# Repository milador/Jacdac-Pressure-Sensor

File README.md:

# Jacdac-Pressure-Sensor
A <a href="https://microsoft.github.io/jacdac-docs/">Jacdac</a> Pressure Sensor Module based on <a href="https://www.st.com/en/mems-and-sensors/lps33hw.html">LPS33HW</a> Absolute digital Pressure Sensor.

## Jacdac Dashboard: 

## Top View: 

## Bottom View:

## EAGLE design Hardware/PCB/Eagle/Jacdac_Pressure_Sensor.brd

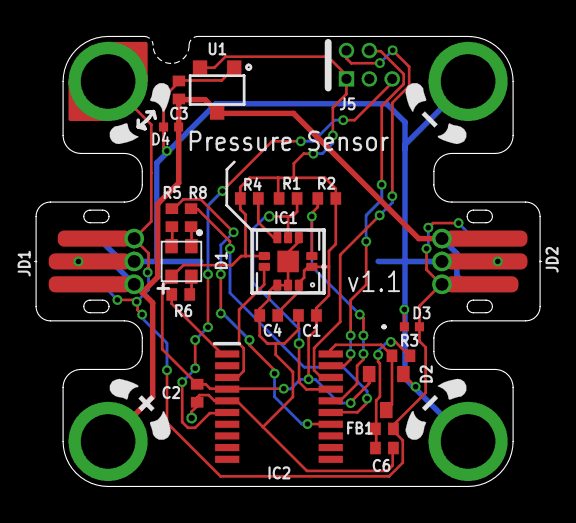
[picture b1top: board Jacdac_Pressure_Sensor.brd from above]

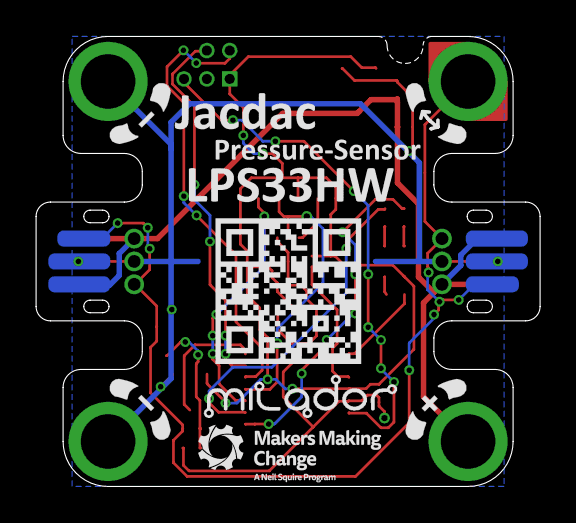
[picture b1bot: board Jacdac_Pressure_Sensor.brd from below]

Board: 2 copper layers, 28.0 x 25.0 mm, 32 parts (5 on the bottom side), 19 nets.

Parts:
C1, C4: 100nF; 0402
C2, C3: 4.7uF; 0402
C6: 33pF; 0402
D1: C108793; LED-RGB-2121
D2: BAT54S-23-3; SOT23-3
D3, D4: RCLAMP0521PATCT; DIODE-ZENER-0402
FB1: 1k@100MHz; 0402
IC1: LPS33HWTR; PQFN60P330X330X290-11N
IC2: STM32G030F6P6; SOP65P640X120-20N
J1: JD; M3-HOLE-DATA
J2: PWR; M3-HOLE-PWR
J3, J4: GND; M3-HOLE-GND
J5: HACK-CONNECT-5; HC5-22-62
JD1, JD2: JACDAC-EDGE-OUTIE; JD-EDGE-OUTIE
LABEL_DEVICE: MILADOR-JACDAC-DEVICE-PS; JACDAC-PRESSURE-SENSOR
LABEL_LOGO1: MILADOR-LOGO-SM; MILADOR_LOGO2
LABEL_LOGO2: MMC_LOGO-XSM; MMC_X-SMALL_LOGO
LABEL_LPS33: MILADOR-JACDAC-DEVICE-LPS33HW; JACDAC-LPS33HW
LABEL_QRCODE: MILADOR-QR-CODE-JACDAC-GITHUB-PS; MILADOR_QR_JACDAC_PS
R1, R2, R4: 10k; 0402
R3, R5: 220R; 0402
R6: 470R; 0402
R8: 150R; 0402
U1: XC6206; SOT23-3-W

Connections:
GND: C1.2, C2.2, C3.2, C4.2, C6.2, D2.1, D3.1, D4.1, IC1.3, IC1.8, IC1.9, IC1.EP, IC2.5, J3.H, J4.H, J5.3, JD1.2, JD1.5, JD1.P$2, JD1.P$4, JD2.2, JD2.5, JD2.P$2, JD2.P$4, U1.1
INT: IC1.7, IC2.3
JD: D2.3, IC2.20, R3.1
JD5V: C3.1, D4.2, J2.H, JD1.3, JD1.4, JD1.P$1, JD2.3, JD2.4, JD2.P$1, U1.3
JDF: D3.2, FB1.2, J1.H, JD1.1, JD1.6, JD1.P$3, JD2.1, JD2.6, JD2.P$3
LED_B: IC2.1, R6.1
LED_G: IC2.14, R5.1
LED_R: IC2.15, R8.1
unnamed: C6.1, FB1.1, R3.2
unnamed: D1.B-, R6.2
unnamed: D1.R-, R8.2
unnamed: D1.G-, R5.2
RESET: IC2.6, J5.5
SA0: IC1.5, R4.1
SCL: IC1.2, IC2.16, R2.1
SDA: IC1.4, IC2.17, R1.1
SWCLK: IC2.19, J5.4
SWDIO: IC2.18, J5.2
VCC: C1.1, C2.1, C4.1, D1.PLUS, D2.2, IC1.1, IC1.6, IC1.10, IC2.4, J5.1, R1.2, R2.2, R4.2, U1.2

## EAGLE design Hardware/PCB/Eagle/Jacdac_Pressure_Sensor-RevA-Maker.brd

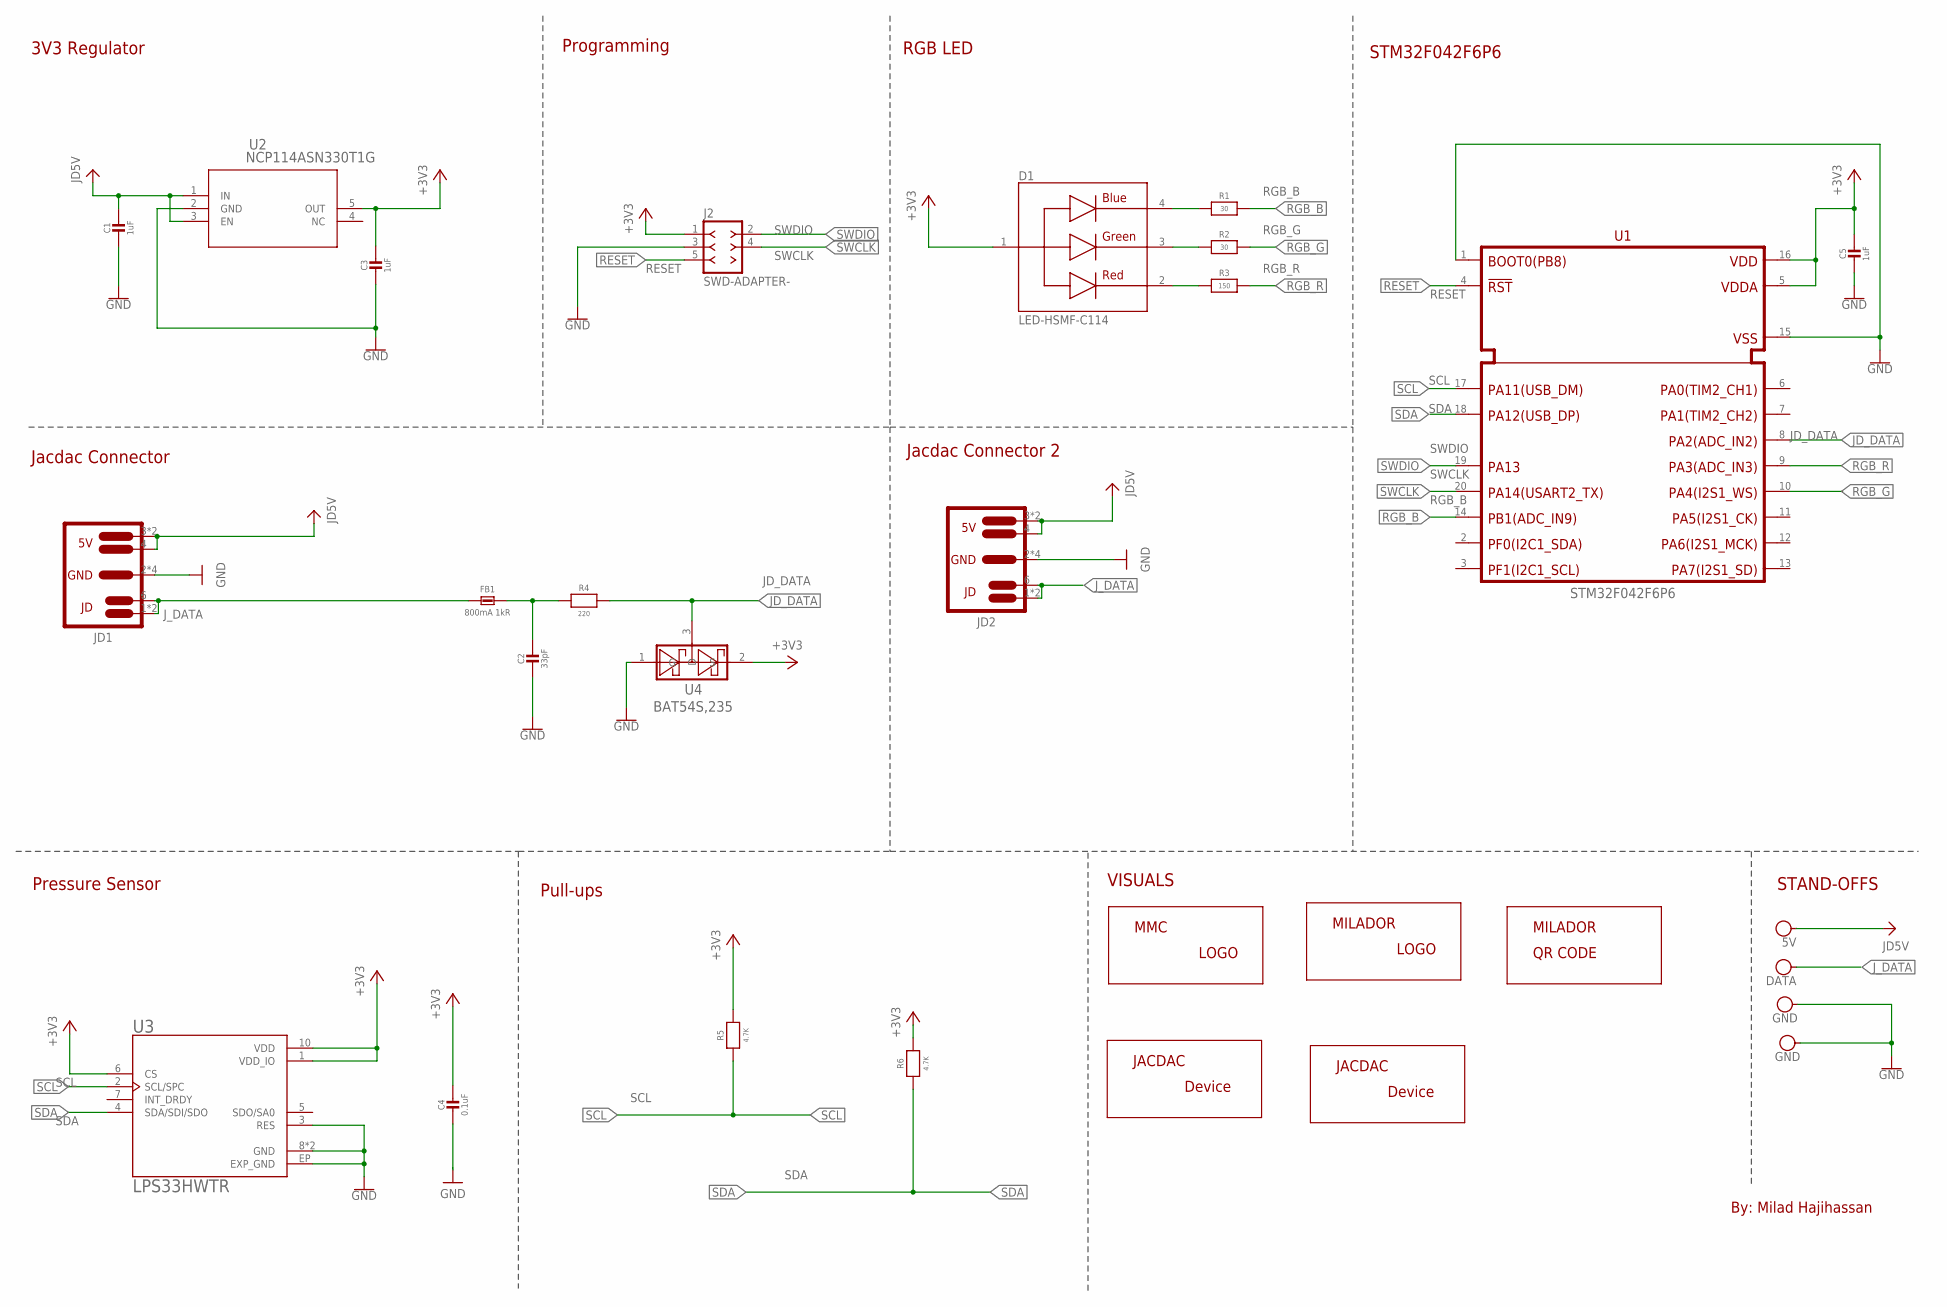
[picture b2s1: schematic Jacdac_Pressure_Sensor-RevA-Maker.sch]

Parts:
C1, C3: 1uF; 0603-NO
C2: 33pF; 0603
C4: 0.1uF; 0603-NO
C5: 1uF; 0603
D1: LED-HSMF-C114; DIOSC160X150X35-4N
FB1: 800mA 1kR; 0603-NO
J2: SWD-ADAPTER-; SWD-ADAPTER
J3: 5V; M3-HOLE-PWR-OUTL
J4: DATA; M3-HOLE-DATA-NOTCH
J5, J6: GND; M3-HOLE-GND
JD1, JD2: JACDAC-EDGE-OUTIE; JD-EDGE-OUTIE
LABEL_JACDAC_PS: MILADOR-JACDAC-DEVICE-PS; JACDAC-PRESSURE-SENSOR
LABEL_LPS33HW: MILADOR-JACDAC-DEVICE-LPS33HW; JACDAC-LPS33HW
LABEL_MILADOR: MILADOR-LOGO-; MILADOR_LOGO1
LABEL_QR_CODE: MILADOR-QR-CODE-JACDAC-GITHUB-PS; MILADOR_QR_JACDAC_PS
MMC_LOGO: MMC_LOGO-XSM; MMC_X-SMALL_LOGO
R1, R2: 30; 0603
R3: 150; 0603
R4: 220; 0603
R5, R6: 4.7K; 0603
U1: STM32F042F6P6; TSSOP20
U2: NCP114ASN330T1G; TSOP-5_ONS
U3: LPS33HWTR; PQFN60P330X330X290-11N
U4: BAT54S,235; SOT23-3

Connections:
+3V3: C3.1, C4.1, C5.1, D1.1, J2.1 (VCC_1), R5.2, R6.2, U1.5 (VDDA), U1.16 (VDD), U2.5 (OUT), U3.1 (VDD_IO), U3.6 (CS), U3.10 (VDD), U4.2 (S)
GND: C1.2, C2.2, C3.2, C4.2, C5.2, J2.3 (GND_3), J5.H, J6.H, JD1.2 (1), JD1.5 (1), JD1.P$2 (1), JD1.P$4 (1), JD2.2 (1), JD2.5 (1), JD2.P$2 (1), JD2.P$4 (1), U1.1 (BOOT0), U1.15 (VSS), U2.2 (GND), U3.3 (RES), U3.8 (GND), U3.9 (GND), U3.EP (EXP_GND), U4.1 (G)
JD5V: C1.1, J3.H, JD1.3, JD1.4, JD1.P$1 (3), JD2.3, JD2.4, JD2.P$1 (3), U2.1 (IN), U2.3 (EN)
JD_DATA: R4.2, U1.8 (PA2), U4.3 (D)
J_DATA: FB1.2, J4.H, JD1.1 (2), JD1.6, JD1.P$3 (2), JD2.1 (2), JD2.6, JD2.P$3 (2)
unnamed: D1.4, R1.1
unnamed: D1.3, R2.1
unnamed: D1.2, R3.1
unnamed: C2.1, FB1.1, R4.1
RESET: J2.5 (RESET_5), U1.4 (!RST)
RGB_B: R1.2, U1.14 (PB1)
RGB_G: R2.2, U1.10 (PA4)
RGB_R: R3.2, U1.9 (PA3)
SCL: R5.1, U1.17 (PA11), U3.2 (SCL/SPC)
SDA: R6.1, U1.18 (PA12), U3.4 (SDA/SDI/SDO)
SWCLK: J2.4 (SWCLK_4), U1.20 (PA14)
SWDIO: J2.2 (SWDIO_2), U1.19 (PA13)

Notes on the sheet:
By: Milad Hajihassan
STAND-OFFS
VISUALS
Programming
3V3 Regulator
RGB LED
Jacdac Connector
Pressure Sensor
Pull-ups
Jacdac Connector 2
STM32F042F6P6

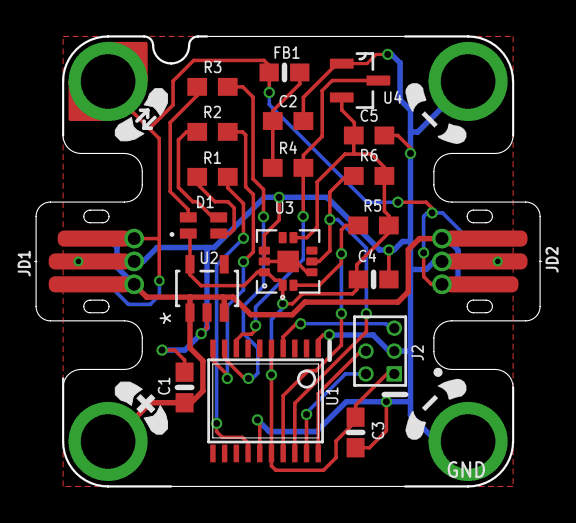
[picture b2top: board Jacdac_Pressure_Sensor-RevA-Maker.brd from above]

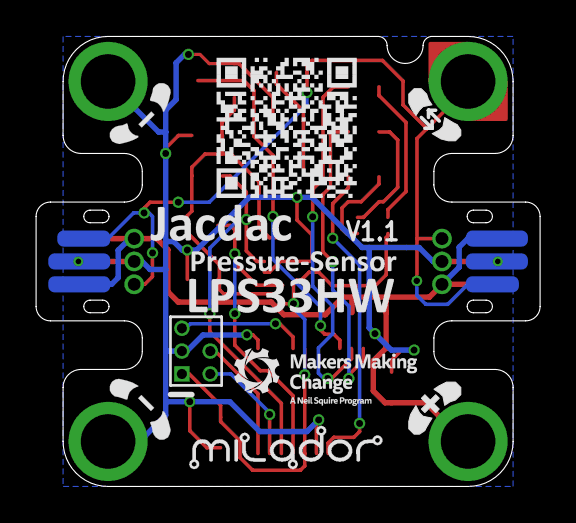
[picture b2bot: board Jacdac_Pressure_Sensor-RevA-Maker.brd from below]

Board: 2 copper layers, 28.0 x 25.0 mm, 29 parts (5 on the bottom side), 17 nets.

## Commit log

2021-09-15 Added Initial design
2021-09-15 Updated readme file
2021-09-17 Updated PCB files
2021-09-18 Updated Maker version
2022-02-20 Updated design
    Use I2C instead of SPI
2022-02-28 Updated files
2022-03-20 Corrected Capacitor values
2022-03-27 Updated main design
    Centering the sensor
2022-03-29 Updated PCB
2022-03-30 Added Additional ground via
2022-06-23 Updated design : Centered Pressure Sensor
2022-06-23 Updated gerber files
2022-07-06 Added version 1.0
2022-07-07 Updated BOM
2022-07-09 Updated RevB
2022-07-13 Updated RevB design to match pinouts of other Jacdac modules
2022-07-14 Updated images
2022-07-14 Updated board.pdf
2022-07-14 Updated components value
2022-08-10 Updated BOM for SMT
2022-10-15 Updated design : Added CS trace
2022-10-15 Updated CPL
2022-10-15 Updated revision A
2022-10-20 Updated RevB : Added Pull-Up to SA0
2022-10-20 Added RevC : Added ESD protection diodes
2022-11-30 Added gerber and cpl files
2022-11-30 Added RevC BOM
2022-11-30 Updated documentation and files to freeze the design V1.1

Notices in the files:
parts and their libraries:
COPYRIGHT: Copyright (C) 2021 Ultra Librarian. All rights reserved.
SparkFun-PowerSymbols: Licensing: Creative Commons ShareAlike 4.0 International - https://creativecommons.org/licenses/by-sa/4.0
